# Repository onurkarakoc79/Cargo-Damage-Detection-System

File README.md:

# Cargo Damage Detection System

## Project Overview
This project is designed to detect and analyze potential causes of damage to packages during transportation by cargo firms. By monitoring environmental factors such as **G-force, pressure, moisture, and temperature**, the system determines whether the package has been mishandled or subjected to conditions likely to cause damage.

The system records data when a **threshold G-force** is exceeded, indicating a possible impact or mishandling event. The collected data is stored on an **SD card** for later analysis to identify the environmental conditions leading to the damage.

## Features
- **G-Force Detection**: Continuously monitors acceleration and triggers data logging when a predefined threshold is exceeded.
- **Environmental Monitoring**: Records pressure, moisture, and temperature readings to identify potential environmental causes of damage.
- **Data Logging**: Saves event data to an SD card for post-incident analysis.
- **Threshold-Based Trigger**: Optimized for efficient power consumption by only logging data during significant events.

## Components
### Hardware
- G-force sensor: **MPU6050**
- Environmental sensors: **BME280** for pressure, temperature, and humidity
- Real-Time Clock: **DS1302 RTC**
- Microcontroller: **ESP32S3**
- SD card module for data storage
- Power source (battery or USB)

### Software
- Code written in **C++** for microcontroller programming
- **Arduino IDE** or **PlatformIO** used for development and debugging
- Libraries for sensor interfacing, real-time clock, and SD card handling

## How It Works
1. The system initializes all sensors and prepares for data collection.
2. **G-force monitoring**: The **MPU6050** continuously checks for motion events exceeding the threshold.
3. When motion is detected, environmental data is collected from the **BME280** (temperature, pressure, and humidity) and the current timestamp from the **DS1302 RTC**.
4. Data is formatted into a message and stored on the **SD card** in CSV format for later analysis.
5. The system then enters a low-power sleep mode until the next event.

## Installation and Setup
### Hardware Assembly
1. Connect the **MPU6050** to the ESP32S3 via I2C (SDA and SCL).
2. Connect the **BME280** to the ESP32S3 via I2C.
3. Connect the **DS1302 RTC** to the ESP32S3 using the RTC data, clock, and reset pins.
4. Attach the SD card module to the ESP32S3.
5. Ensure proper power supply connections to all components as per the provided PCB schematic.

### Software Setup
1. Clone this repository to your local machine:
   ```bash
   git clone https://github.com/onurkarakoc79/Cargo-Damage-Detection-System
   ```
2. Open the project in the Arduino IDE or PlatformIO.
3. Install the required libraries:
   - `Wire.h` for I2C communication
   - `Adafruit_Sensor.h` for BME280
   - Custom libraries for **MPU6050**, **DS1302 RTC**, and **SDCard**
4. Upload the code to your ESP32S3 microcontroller.
5. Insert an SD card into the SD card module.

## Data Format
The system logs data in **CSV format** for easy analysis. Each log entry includes the following fields:
- **Timestamp**: Current time recorded by the RTC
- **Temperature (°C)**: Ambient temperature
- **Pressure (hPa)**: Barometric pressure
- **Altitude (m)**: Altitude derived from pressure
- **Humidity (%)**: Relative humidity
- **Acceleration (g)**: X, Y, and Z-axis acceleration values

### Example Data Format
| Timestamp         | Temperature (°C) | Pressure (hPa) | Altitude (m) | Humidity (%) | AccX (g) | AccY (g) | AccZ (g) |
|--------------------|-------------------|----------------|--------------|--------------|----------|----------|----------|
| 2025-01-25 12:00  | 22.5              | 1013.25        | 50.2         | 45           | 0.98     | -0.12    | -1.19    |
| 2025-01-25 12:01  | 23.0              | 1013.30        | 50.3         | 46           | 1.12     | 0.08     | -1.22    |

## Applications
- Package monitoring for logistics and cargo firms
- Root cause analysis for damaged goods
- Real-time quality control in shipping environments

## Contribution
Contributions are welcome! Feel free to open an issue or submit a pull request to improve this project.

## License
This project is licensed under the MIT License. See the `LICENSE` file for more details.

## Contact

If you have any questions, feedback, or inquiries related to the project, feel free to reach out to me:

My personal mail: onurkarakoc79@gmail.com

I appreciate your interest in my projects and look forward to collaborating with you in the fascinating field of scientific exploration and discovery.

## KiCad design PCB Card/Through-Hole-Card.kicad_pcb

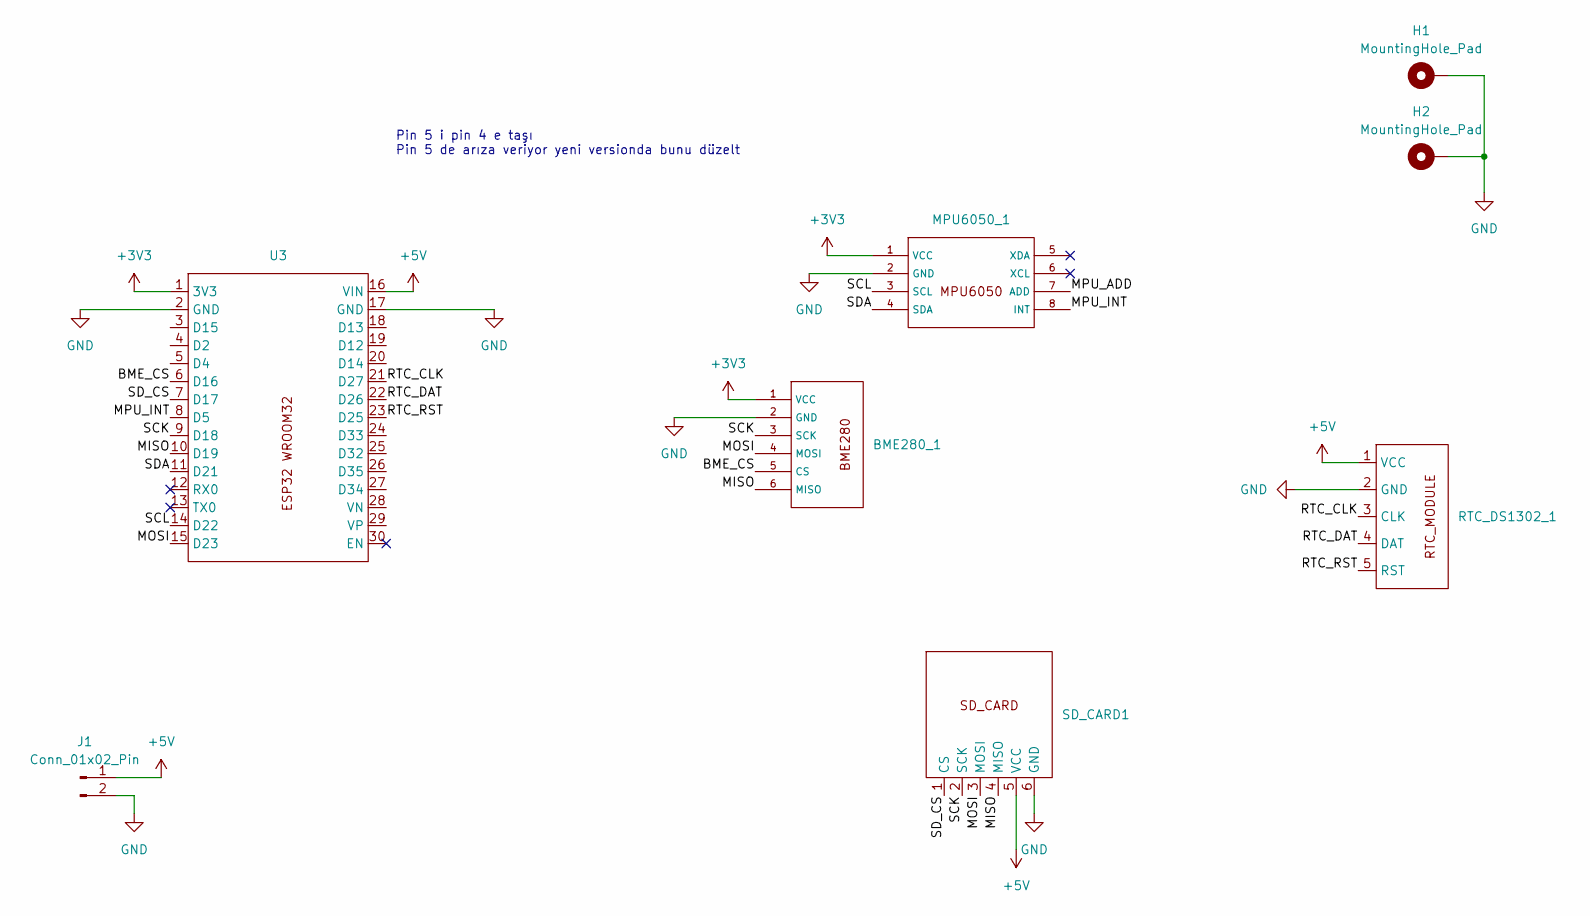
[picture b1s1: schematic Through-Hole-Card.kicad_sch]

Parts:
BME280_1: BME280
H1, H2: MountingHole_Pad; MountingHole_2.2mm_M2_Pad
J1: Conn_01x02_Pin; PinHeader_1x02_P2.54mm_Vertical
MPU6050_1: MPU6050
RTC_DS1302_1: DS1302_RTC_MODULE
SD_CARD1: SDCard
U3: ESP32-WROOM-32

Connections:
+3V3: BME280_1.1 (VCC), MPU6050_1.1 (VCC), U3.1 (3V3)
+5V: J1.1, RTC_DS1302_1.1 (VCC), SD_CARD1.5 (VCC), U3.16 (VIN)
/BME_CS: BME280_1.5 (CS), U3.6 (D16)
/MISO: BME280_1.6 (MISO), SD_CARD1.4 (MISO), U3.10 (D19)
/MOSI: BME280_1.4 (MOSI), SD_CARD1.3 (MOSI), U3.15 (D23)
/MPU_ADD: MPU6050_1.7 (ADD)
/MPU_INT: MPU6050_1.8 (INT), U3.8 (D5)
/RTC_CLK: RTC_DS1302_1.3 (CLK), U3.21 (D27)
/RTC_DAT: RTC_DS1302_1.4 (DAT), U3.22 (D26)
/RTC_RST: RTC_DS1302_1.5 (RST), U3.23 (D25)
/SCK: BME280_1.3 (SCK), SD_CARD1.2 (SCK), U3.9 (D18)
/SCL: MPU6050_1.3 (SCL), U3.14 (D22)
/SDA: MPU6050_1.4 (SDA), U3.11 (D21)
/SD_CS: SD_CARD1.1 (CS), U3.7 (D17)
GND: BME280_1.2 (GND), H1.1, H2.1, J1.2, MPU6050_1.2 (GND), RTC_DS1302_1.2 (GND), SD_CARD1.6 (GND), U3.2 (GND), U3.17 (GND)

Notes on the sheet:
Pin 5 i pin 4 e taşı Pin 5 de arıza veriyor yeni versionda bunu düzelt

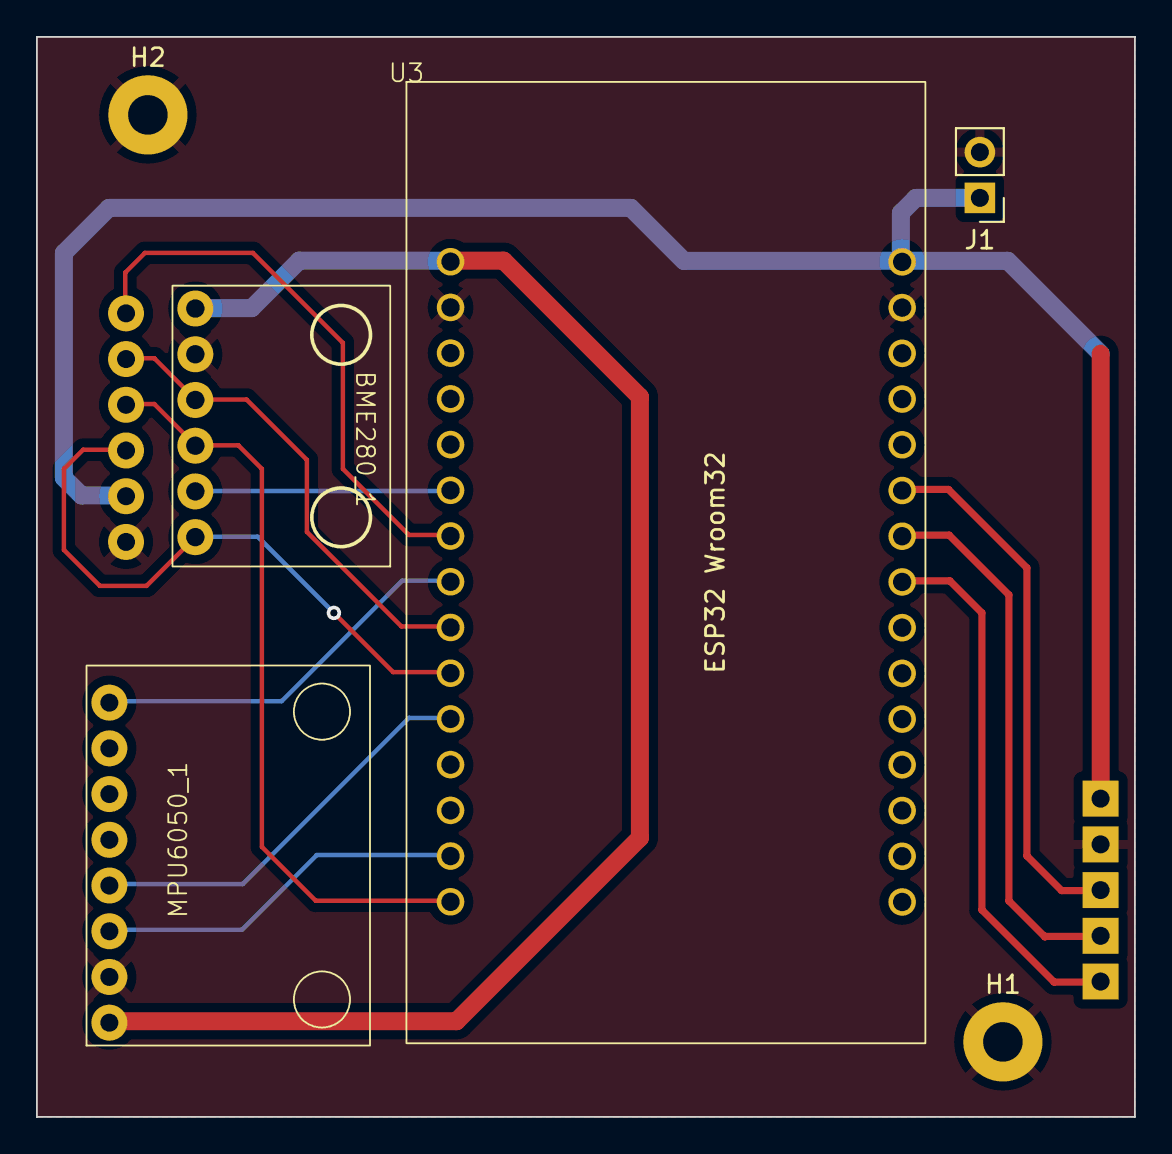
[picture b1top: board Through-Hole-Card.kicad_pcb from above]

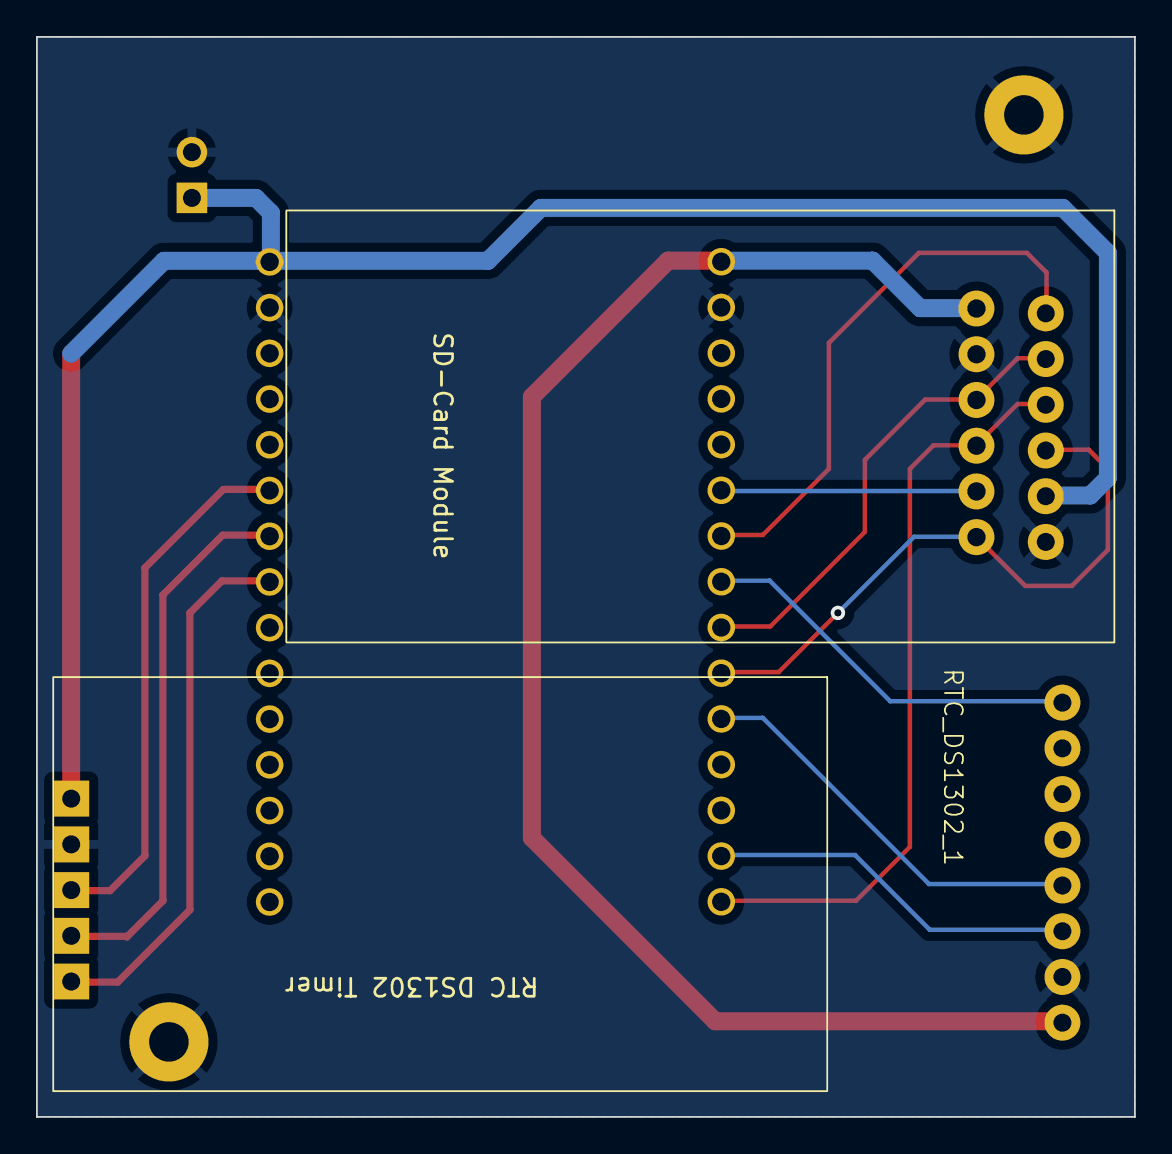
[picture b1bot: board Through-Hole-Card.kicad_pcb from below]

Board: 2 copper layers, 61.0 x 60.0 mm, 8 parts (2 on the bottom side), 14 nets.

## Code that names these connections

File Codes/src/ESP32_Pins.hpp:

#ifndef ESP32_PINS_HPP
#define ESP32_PINS_HPP


#define BME_CS_PIN 16
#define SD_CS_PIN 17
#define MPU_INT_PIN GPIO_NUM_4


#define ESP_MOSI 23
#define ESP_SCK 18
#define ESP_MISO 19 

#define RTC_CLK_PIN 27
#define RTC_DATA_PIN 26
#define RTC_RST_PIN 25




#define SCL_PIN 22
#define SDA_PIN 21






#endif
